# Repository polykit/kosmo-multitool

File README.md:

# Kosmo Multitool

This repository contains schematics, PCB and source code for a synthesizer module in Kosmo format. This module consists of an Arduino Nano Every, CV and gate input and output options, MIDI, rotary encoder and an OLED display. It is meant as a development platform for DIY synthesizer enthusiasts.

Here is a full list of features:
- 4x CV input (0-10V)
- 4x CV output (0-10V)
- 4x gate/trigger in
- 4x gate/trigger out
- 1.3" OLED display
- DIN serial MIDI in/through/out
- Rotary encoder with switch
- 3 switches
- 2 LEDs

## Modules

- ADSR
- Arpeggiator
- MIDI to CV
- Multiple
- Quantizer

## Building

Gerbers for the main PCB can be found [here](plots) and for the front panel [here](panel/plots).

### BOM

|Reference                                                  |Quantity|Value                |Comment                                           |
|-----------------------------------------------------------|--------|---------------------|--------------------------------------------------|
|A1                                                         |1       |Arduino Nano Every   |                                                  |
|C1 C2 C3 C4 C6 C7 C8                                       |7       |100n                 |                                                  |
|C5 C9 C10                                                  |3       |10uF                 |                                                  |
|D17 D18                                                    |2       |LED 5mm              |                                                  |
|D1 D2 D3 D4 D5 D6 D7 D8 D9 D10 D11 D12 D13 D14 D15 D16 D19 |17      |1N4148               |                                                  |
|FB1 FB2                                                    |2       |Ferrite Bead         |                                                  |
|J1                                                         |1       |MIDI_IN              |Molex KK 2.54mm 2 pin                             |
|J10                                                        |1       |CV_OUT               |Molex KK 2.54mm 5 pin                             |
|J2                                                         |1       |Display I2C          |OLED display 1.3" 128x64 I2C SH1106               |
|J3                                                         |1       |GATE_IN              |Molex KK 2.54mm 5 pin                             |
|J4                                                         |1       |GATE_OUT             |Molex KK 2.54mm 5 pin                             |
|J5                                                         |1       |ADS1115 breakout     |ADC, pin order: VCC GND SCL SDA ADDR ALERT A B C D|
|J6                                                         |1       |MIDI_THRU            |Molex KK 2.54mm 2 pin                             |
|J7                                                         |1       |MIDI_OUT             |Molex KK 2.54mm 2 pin                             |
|J8                                                         |1       |MCP4728 breakout     |DAC, pin order: VCC GND SCL SDA LDAC READY A B C D|
|J9                                                         |1       |CV_IN                |Molex KK 2.54mm 5 pin                             |
|POWER1                                                     |1       |POWER                |IDC 10 pin                                        |
|R1 R2 R3 R4 R11 R12 R15 R16                                |8       |1k*                  |                                                  |
|R5 R8 R13 R14                                              |4       |22k                  |                                                  |
|R9 R10 R17 R18                                             |4       |33k                  |                                                  |
|R25 R26 R27 R29 R30 R31 R32 R33                            |8       |220                  |                                                  |
|R28 R34 R35 R36 R37                                        |5       |10k                  |                                                  |
|R6 R7 R19 R20 R21 R22 R23 R24                              |8       |1k                   |                                                  |
|SW1 SW2 SW3                                                |3       |SW_Push              |Tactile Push Button 6x6x15mm                      |
|SW4                                                        |1       |Rotary_Encoder_Switch|Rotary encoder with switch, 20mm                  |
|U1                                                         |1       |TL074                |                                                  |
|U2                                                         |1       |74LS14               |                                                  |
|U3                                                         |1       |6N137                |                                                  |
|U4                                                         |1       |L7805                |                                                  |
|                                                           |        |Pin sockets, 2.54mm  |Needed for the Arduino, OLED display, ADC and DAC |
|                                                           |16      |Jack sockets 6.35mm  |                                                  |
|                                                           |3       |DIN MIDI sockets     |                                                  |

\* match in pairs to get more accurate ADC readings

## Installation and calibration

Clone the repository and open up the `src/main` folder in the Arduino IDE or whatever you use for compiling. You need to install the libraries mentioned below into you Arduino library folder. The ADC and the DAC need calibration to get proper results.

### ADC calibration
Set `CALIBRATE_CV_IN` variable in main file to `1`. Apply a fixed, known voltage to CV1 input, eg. 5.000V. On USB serial console (9600 baud) you get the actual reading from the ADC. Calculate the correction factor `FIXED VOLTAGE / ACTUAL VOLTAGE`, eg. `5.000 / 4.9884 = 1.0023`. Enter the value in the CV_IN_CORRECTION array in the top lines of `main.ino`. Repeat this procedure for all CV inputs. In the end it should look something like this:
```
float CV_IN_CORRECTION[4] = {0.9995f, 0.9956f, 1.0013f, 1.0009f};
```
Notice the trailing `f` to tell the compiler that these are float values. Don't forget to set `CALIBRATE_CV_IN` back to `0`.

### DAC calibration
Make sure to calibrate the ADC first. Set `CALIBRATE_CV_OUT` variable in main file to `1`. Plug in patch cables from all four CV inputs to the CV outputs. Calibration is done automatically and stored in a look-up table. Set `CALIBRATE_CV_OUT` back to `0`. This step is only needed once, from now on calibration values are loaded from EEPROM on start up.

## Development

Source code is in `src/main`. If you want to develop your own module just copy the files `example_module.h` and `example_module.ino` and rename all functions and variables that are globally available. Include your header file in the `main.ino` file and add your entry to the main menu. Take a look at the already existing modules on how it works in general. If you created a nice module please file a pull request and I would be happy to merge it.

## Libraries

https://github.com/adafruit/Adafruit_MCP4728

https://github.com/adafruit/Adafruit_ADS1X15

https://github.com/olikraus/u8g2

https://github.com/FortySevenEffects/arduino_midi_library

https://github.com/neu-rah/ArduinoMenu

https://github.com/thomasfredericks/Bounce2

https://github.com/mathertel/RotaryEncoder

https://github.com/ivanseidel/LinkedList

## References

https://www.lookmumnocomputer.com/modular

https://www.ti.com/lit/ds/symlink/ads1115.pdf

http://ww1.microchip.com/downloads/en/devicedoc/22187e.pdf

https://github.com/DylanMeeus/GoAudio

## License

This work is licensed under a [Creative Commons Attribution-NonCommercial 4.0 International License](http://creativecommons.org/licenses/by-nc/4.0/).

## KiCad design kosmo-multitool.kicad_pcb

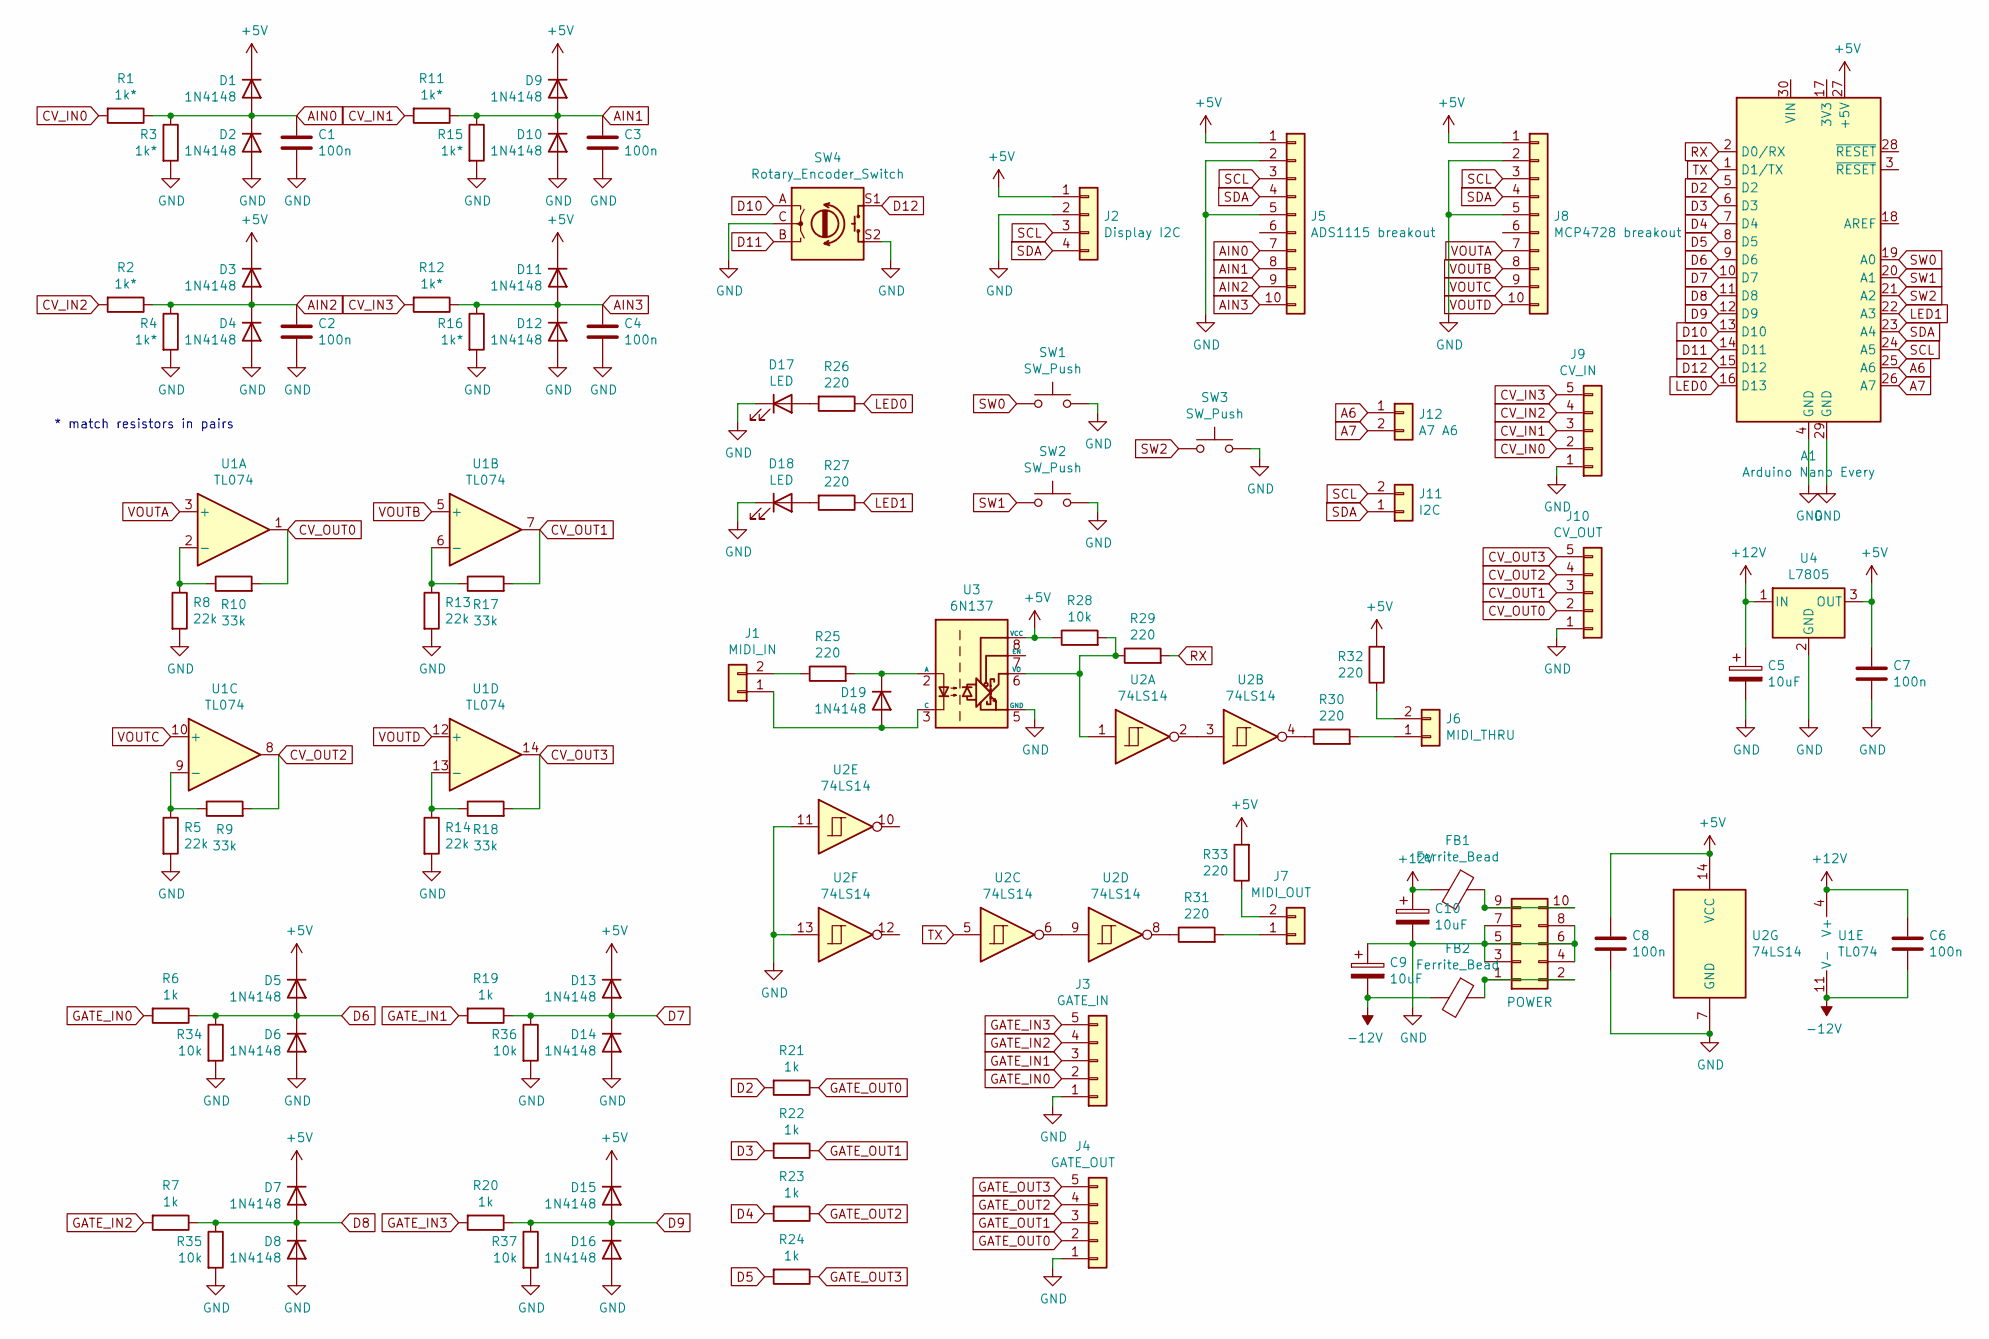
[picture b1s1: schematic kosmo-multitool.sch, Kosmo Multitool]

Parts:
A1: Arduino Nano Every; Arduino_Nano
C1, C2, C3, C4, C6, C7, C8: 100n; C_Disc_D5.0mm_W2.5mm_P5.00mm
C5, C9, C10: 10uF; CP_Radial_D5.0mm_P2.50mm
D1, D2, D3, D4, D5, D6, D7, D8, D9, D10, D11, D12, D13, D14, D15, D16, D19: 1N4148; D_DO-35_SOD27_P7.62mm_Horizontal
D17, D18: LED; LED_D5.0mm
FB1, FB2: Ferrite_Bead; R_Axial_DIN0207_L6.3mm_D2.5mm_P10.16mm_Horizontal
J1: MIDI_IN; Molex_KK-254_AE-6410-02A_1x02_P2.54mm_Vertical
J2: Display I2C; PinHeader_1x04_P2.54mm_Vertical
J3: GATE_IN; Molex_KK-254_AE-6410-05A_1x05_P2.54mm_Vertical
J4: GATE_OUT; Molex_KK-254_AE-6410-05A_1x05_P2.54mm_Vertical
J5: ADS1115 breakout; PinHeader_1x10_P2.54mm_Vertical
J6: MIDI_THRU; Molex_KK-254_AE-6410-02A_1x02_P2.54mm_Vertical
J7: MIDI_OUT; Molex_KK-254_AE-6410-02A_1x02_P2.54mm_Vertical
J8: MCP4728 breakout; PinHeader_1x10_P2.54mm_Vertical
J9: CV_IN; Molex_KK-254_AE-6410-05A_1x05_P2.54mm_Vertical
J10: CV_OUT; Molex_KK-254_AE-6410-05A_1x05_P2.54mm_Vertical
J11: I2C; PinHeader_1x02_P2.54mm_Vertical
J12: A7 A6; PinHeader_1x02_P2.54mm_Vertical
POWER1: POWER; IDC-Header_2x05_P2.54mm_Vertical
R1, R2, R3, R4, R11, R12, R15, R16: 1k*; R_Axial_DIN0207_L6.3mm_D2.5mm_P10.16mm_Horizontal
R5, R8, R13, R14: 22k; R_Axial_DIN0207_L6.3mm_D2.5mm_P10.16mm_Horizontal
R6, R7, R19, R20, R21, R22, R23, R24: 1k; R_Axial_DIN0207_L6.3mm_D2.5mm_P10.16mm_Horizontal
R9, R10, R17, R18: 33k; R_Axial_DIN0207_L6.3mm_D2.5mm_P10.16mm_Horizontal
R25, R26, R27, R29, R30, R31, R32, R33: 220; R_Axial_DIN0207_L6.3mm_D2.5mm_P10.16mm_Horizontal
R28, R34, R35, R36, R37: 10k; R_Axial_DIN0207_L6.3mm_D2.5mm_P10.16mm_Horizontal
SW1, SW2, SW3: SW_Push; SW_PUSH_6mm_H13mm
SW4: Rotary_Encoder_Switch; RotaryEncoder_Alps_EC11E-Switch_Vertical_H20mm
U1: TL074; DIP-14_W7.62mm_Socket_LongPads
U2: 74LS14; DIP-14_W7.62mm_Socket_LongPads
U3: 6N137; DIP-8_W7.62mm_Socket_LongPads
U4: L7805; TO-220-3_Vertical

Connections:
+5V: A1.27 (+5V), C7.1, C8.1, D1.1 (K), D3.1 (K), D5.1 (K), D7.1 (K), D9.1 (K), D11.1 (K), D13.1 (K), D15.1 (K), J2.1, J5.1, J8.1, R28.1, R32.2, R33.2, U2.14 (VCC), U3.8 (VCC), U4.3 (OUT)
+12V: C5.1, C6.1, C10.1, FB1.2, U1.4 (V+), U4.1 (IN)
-12V: C6.2, C9.2, FB2.2, U1.11 (V-)
A6: A1.25 (A6), J12.1
A7: A1.26 (A7), J12.2
AIN0: C1.1, D1.2 (A), D2.1 (K), J5.7, R1.1, R3.1
AIN1: C3.1, D9.2 (A), D10.1 (K), J5.8, R11.1, R15.1
AIN2: C2.1, D3.2 (A), D4.1 (K), J5.9, R2.1, R4.1
AIN3: C4.1, D11.2 (A), D12.1 (K), J5.10, R12.1, R16.1
CV_IN0: J9.2, R1.2
CV_IN1: J9.3, R11.2
CV_IN2: J9.4, R2.2
CV_IN3: J9.5, R12.2
CV_OUT0: J10.2, R10.2, U1.1
CV_OUT1: J10.3, R17.2, U1.7
CV_OUT2: J10.4, R9.2, U1.8
CV_OUT3: J10.5, R18.2, U1.14
D2: A1.5 (D2), R21.2
D3: A1.6 (D3), R22.2
D4: A1.7 (D4), R23.2
D5: A1.8 (D5), R24.2
D6: A1.9 (D6), D5.2 (A), D6.1 (K), R6.1, R34.1
D7: A1.10 (D7), D13.2 (A), D14.1 (K), R19.1, R36.1
D8: A1.11 (D8), D7.2 (A), D8.1 (K), R7.1, R35.1
D9: A1.12 (D9), D15.2 (A), D16.1 (K), R20.1, R37.1
D10: A1.13 (D10), SW4.A
D11: A1.14 (D11), SW4.B
D12: A1.15 (D12), SW4.S1
GATE_IN0: J3.2, R6.2
GATE_IN1: J3.3, R19.2
GATE_IN2: J3.4, R7.2
GATE_IN3: J3.5, R20.2
GATE_OUT0: J4.2, R21.1
GATE_OUT1: J4.3, R22.1
GATE_OUT2: J4.4, R23.1
GATE_OUT3: J4.5, R24.1
GND: A1.4 (GND), A1.29 (GND), C1.2, C2.2, C3.2, C4.2, C5.2, C7.2, C8.2, C9.1, C10.2, D2.2 (A), D4.2 (A), D6.2 (A), D8.2 (A), D10.2 (A), D12.2 (A), D14.2 (A), D16.2 (A), D17.1 (K), D18.1 (K), J2.2, J3.1, J4.1, J5.2, J5.5, J8.2, J8.5, J9.1, J10.1, POWER1.3, POWER1.4, POWER1.5, POWER1.6, POWER1.7, POWER1.8, R3.2, R4.2, R5.2, R8.2, R13.2, R14.2, R15.2, R16.2, R34.2, R35.2, R36.2, R37.2, SW1.2, SW2.2, SW3.2, SW4.C, SW4.S2, U2.7 (GND), U2.11, U2.13, U3.5 (GND), U4.2 (GND)
LED0: A1.16 (D13), R26.1
LED1: A1.22 (A3), R27.1
unnamed: D17.2 (A), R26.2
unnamed: D18.2 (A), R27.2
unnamed: D19.1 (K), R25.2, U3.2 (A)
unnamed: D19.2 (A), J1.1, U3.3 (C)
unnamed: FB1.1, POWER1.9, POWER1.10
unnamed: FB2.1, POWER1.1, POWER1.2
unnamed: J1.2, R25.1
unnamed: J6.1, R30.2
unnamed: J6.2, R32.1
unnamed: J7.1, R31.2
unnamed: J7.2, R33.1
unnamed: R5.1, R9.1, U1.9 (-)
unnamed: R8.1, R10.1, U1.2 (-)
unnamed: R13.1, R17.1, U1.6 (-)
unnamed: R14.1, R18.1, U1.13 (-)
unnamed: R28.2, R29.1, U2.1, U3.6 (VO)
unnamed: R30.1, U2.4
unnamed: R31.1, U2.8
unnamed: U2.2, U2.3
unnamed: U2.6, U2.9
RX: A1.2 (D0/RX), R29.2
SCL: A1.24 (A5), J2.3, J5.3, J8.3, J11.2
SDA: A1.23 (A4), J2.4, J5.4, J8.4, J11.1
SW0: A1.19 (A0), SW1.1
SW1: A1.20 (A1), SW2.1
SW2: A1.21 (A2), SW3.1
TX: A1.1 (D1/TX), U2.5
VOUTA: J8.7, U1.3 (+)
VOUTB: J8.8, U1.5 (+)
VOUTC: J8.9, U1.10 (+)
VOUTD: J8.10, U1.12 (+)

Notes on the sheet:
* match resistors in pairs

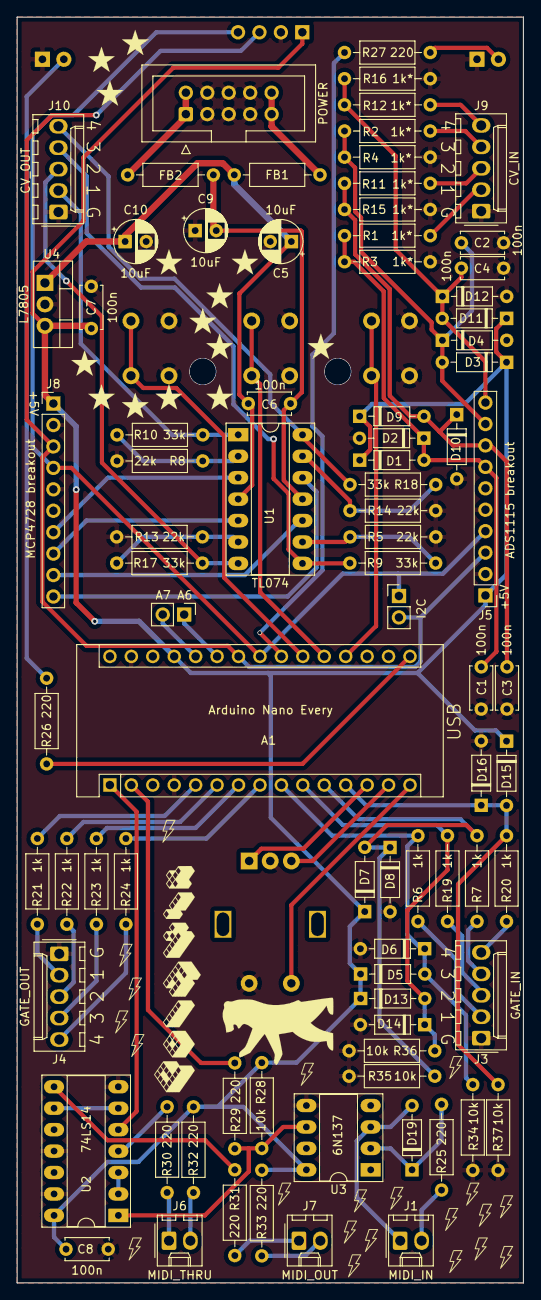
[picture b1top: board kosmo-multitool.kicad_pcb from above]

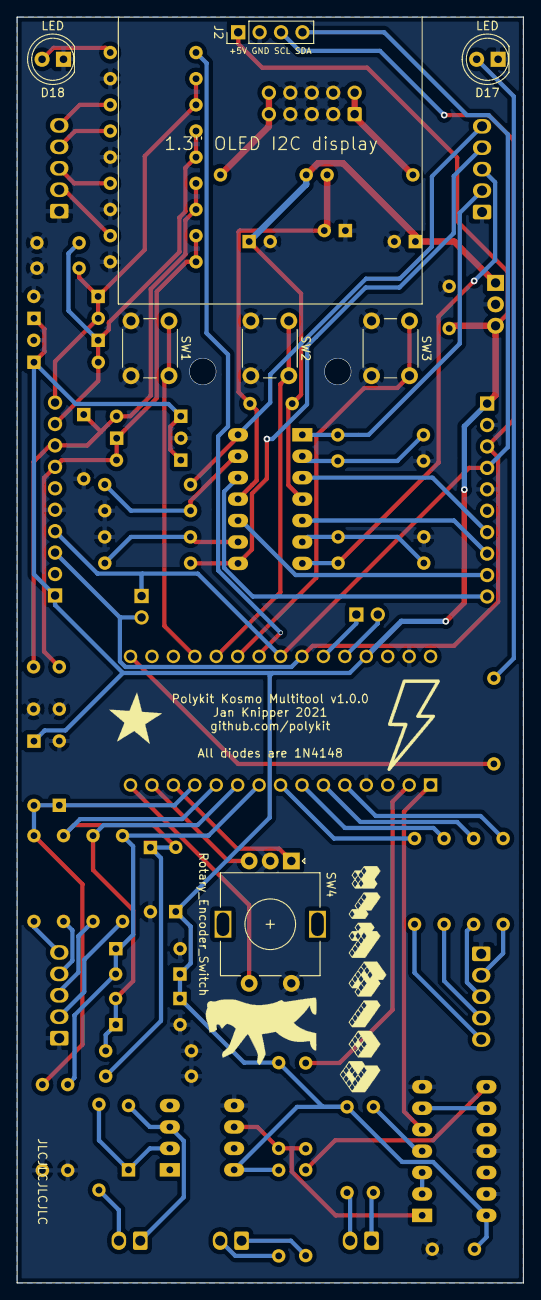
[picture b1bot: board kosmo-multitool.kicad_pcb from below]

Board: 2 copper layers, 60.0 x 150.0 mm, 90 parts (7 on the bottom side), 70 nets.

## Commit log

2021-05-28 Initial import
2021-05-28 Fix menu
2021-05-28 Changes readme
2021-05-29 Add license
2021-05-29 Add hold to arpeggiator
2021-05-29 Add MIDI to CV and multiple
2021-05-30 Add ADSR module
2021-10-08 Add image for modulargrid
2021-10-08 Add small multigrid image
2021-10-08 Add quantizer, readme
